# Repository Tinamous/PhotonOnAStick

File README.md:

# PhotonOnAStick
Particle Photon Prototyping board on a USB Stick

## Currently untested (11 July 2015). PCBs ordered for testing.

## Use Case

* Prototype post breadboard. 
* Connection of sensors, LEDs, SparkFun style breakout boards etc.
* Deployed Thing on a Stick where the Photon may be used to make an internet connected sensor for a room, or lighting or ??? and can be plugged into a USB wall adaptor.
* Using readily available wall plugs board may be connected:
** with the board vertical, Photon facing outwards flat to the wall.
** with the board horizontal, Photon facing upwards. 
* These options makes for a nice option for uplighting (internet controlled nightlight?), or a room sensor.
* Other power adaptors exist, e.g. USB in a multi-gang outlet.

## Usage

* USB powered by plugging into a USB A socket on a USB Wall Adaptor, or A -> Micro B on the Particle Photon. Do not connect both at once.
* Top layer is mainly for 0805 devices (and through hole).
* Bottom layer is for 1206 devices (and through hole).

## Botton (looking at the baord with USB connector to the left)
* A0-A7 Analog signals come out to the option of a round test point (solder connection) via an 0805. Can be resistor, 0 ohm link or ....
* A0-A7 Analog signals also come out to a 1206 package with the other side unconnected so this can have a wire tacked on as needed.
** This arrangement may be used to provide either imput impedance/capacitance filter to the analog signal, 
** or by connecting the unterminated end to GND or 3V3 this can provice half of a potential divider for a sensor - the sensor may be providing the other half.
* +5V, Gnd, Tx and Rx come out to a 1206 only. Allows for a resitor and/or wire tacking.

## Center
* Top layer in the middle is a SO16 package outline, can be used for SO8 or anything that would fit. Pins 1-8 go to connectors by the USB port, 9-16 by the bottom of the Photon.
* Top 2 connectors in the middle of the Photon have +5V, +3V3 and Gnd available.

## Top (looking at the baord with USB connector to the left)
* 3v3, VBat and Gnd brought out to 4 pin connector. Pin 2 unconnected (may be used for polarity).
* D0-D7 connected to 1206 package on bottom layer with other end unconnected available for wire.
* D0-D7 on top layer go to 0805 package which is liked to a second 0805 with the far end connected to ground.
** This arrangement allows D0-D7 to be connected to a (0805) LED then a (0805)current limiting resitor on the top layer
** or to provide a pull down where the input is connected to the middle of the pins 0805 packages.

## Prototyping area (Right hand side looking at the baord with USB connector to the left).
* Top rail is 3v3 from the Photon (3)
* Second rail down is GND (G)
* Bottom rail is +5V (5)
* 3V3 and GND have a 0805 connection for a capacitor.
* Each pair of rows have possible connection for 0805 and 1206 device near the Photon to allow for capacitor, resistor or LED.
* Only power rails are connected hole to hole.
* 8 1206 or 8 * 2 0805s are available on the right, again for LEDs, Sensors, Resistors or Capacitors. 
** The 2x 0805 combination allows for a LED + resistor. Either side of the 1206 or 0805 pair are connected to the pins to the outside of them.

## Spark Photon
* This board is designed for the Particle Photon. It does need headers though.
* The Particle Core (Spark Core) may also be used.

## Eagle Libraries Used:

Particle Photon Library: https://github.com/spark/photon/tree/master/libraries
SparkFun: https://github.com/sparkfun/SparkFun-Eagle-Libraries

## Versioning

* Board will have multiple major versions. e.g.
** V1 A0-A8 1206/0805's unterminated.
** V1.x bug fixes for V1 board.

** V2 A0-A8 1206/0805's terminated with +5 or GND based on layer
** V2.x bug fixes for V2 board.

## Ideas

### Different versions

* Change A0-A8 1206 packages so unconnected end is connected to 
* Much narrower (just room for Photon)
* Wonly - USB port at Top Right corner to allow for top exit wall adaptors where USB socket is perpendicular to the wall.
* Surface mount photon

* Timer version. LED/LCD/OLED dispay. Sensor to allow for setting and starting of timer (Hands free)

## Bugs

* Missing Open Hardware Logo.

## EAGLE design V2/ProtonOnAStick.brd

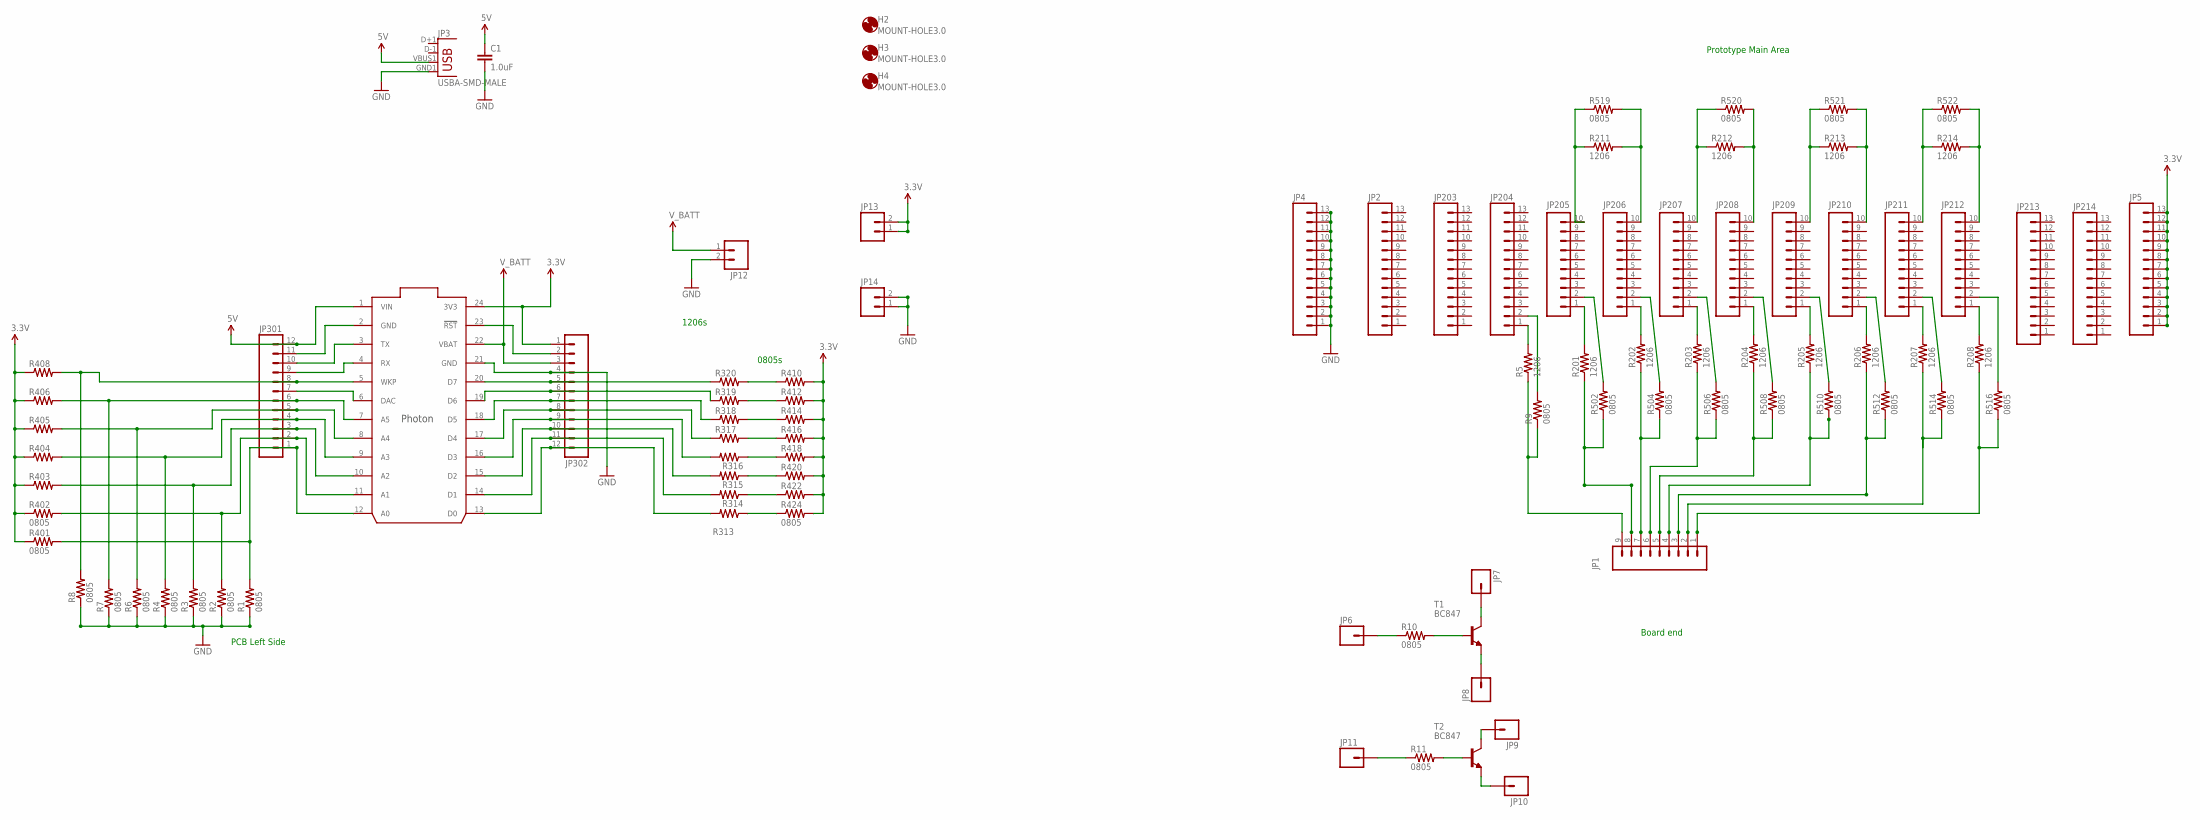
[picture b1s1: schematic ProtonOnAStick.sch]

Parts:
C1: 1.0uF; 0805-CAP
H2, H3, H4: MOUNT-HOLE3.0; 3,0
IC1: PHOTON_WITH_HEADERS; PHOTON
JP1: M09; 1X09
JP2, JP4, JP5, JP203, JP204, JP213, JP214: M13; 1X13
JP3: USBA-SMD-MALE; USB-A-SMT-MALE
JP6, JP7, JP8, JP9, JP10, JP11: M01PTH; 1X01
JP12: M02JST-PTH-2; JST-2-PTH
JP13, JP14: M02PTH; 1X02
JP205, JP206, JP207, JP208, JP209, JP210, JP211, JP212: M10SILK_FEMALE_PTH; 1X10
JP301, JP302: M12PTH; 1X12
R1, R2, R3, R4, R6, R7, R8, R9, R10, R11, R401, R402, R403, R404, R405, R406, R408, R410, R412, R414, R416, R418, R420, R422, R424, R502, R504, R506, R508, R510, R512, R514, R516, R519, R520, R521, R522: 0805
R5, R201, R202, R203, R204, R205, R206, R207, R208, R211, R212, R213, R214, R313, R314, R315, R316, R317, R318, R319, R320: 1206
T1, T2: BC847; SOT23

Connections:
3.3V: IC1.24 (3V3), JP5.1, JP5.2, JP5.3, JP5.4, JP5.5, JP5.6, JP5.7, JP5.8, JP5.9, JP5.10, JP5.11, JP5.12, JP5.13, JP13.1, JP13.2, JP302.1, R401.1, R402.1, R403.1, R404.1, R405.1, R406.1, R408.1, R410.2, R412.2, R414.2, R416.2, R418.2, R420.2, R422.2, R424.2
5V: C1.1, IC1.1 (VIN), JP3.VBUS1 (VBUS), JP301.12
GND: C1.2, IC1.2 (GND), IC1.21 (GND), JP3.GND1 (GND), JP4.1, JP4.2, JP4.3, JP4.4, JP4.5, JP4.6, JP4.7, JP4.8, JP4.9, JP4.10, JP4.11, JP4.12, JP4.13, JP12.2, JP14.1, JP14.2, JP301.11, JP302.4, R1.1, R2.1, R3.1, R4.1, R6.1, R7.1, R8.1
unnamed: JP6.1, R10.1
unnamed: JP206.1, R202.2
unnamed: JP204.1, R5.2
unnamed: IC1.3 (TX), JP301.10
unnamed: IC1.4 (RX), JP301.9
unnamed: IC1.5 (WKP), JP301.8, R8.2, R408.2
unnamed: IC1.6 (DAC), JP301.7
unnamed: IC1.7 (A5), JP301.6, R7.2, R406.2
unnamed: IC1.8 (A4), JP301.5, R6.2, R405.2
unnamed: IC1.9 (A3), JP301.4, R4.2, R404.2
unnamed: IC1.10 (A2), JP301.3, R3.2, R403.2
unnamed: IC1.11 (A1), JP301.2, R2.2, R402.2
unnamed: IC1.12 (A0), JP301.1, R1.2, R401.2
unnamed: JP1.9, R5.1, R9.1
unnamed: R10.2, T1.1 (B)
unnamed: IC1.18 (D5), JP302.7, R318.1
unnamed: IC1.17 (D4), JP302.8, R317.1
unnamed: IC1.16 (D3), JP302.9, R316.2
unnamed: IC1.15 (D2), JP302.10, R315.2
unnamed: IC1.14 (D1), JP302.11, R314.2
unnamed: IC1.13 (D0), JP302.12, R313.2
unnamed: JP209.1, R205.2
unnamed: JP211.2, R514.2
unnamed: IC1.23 (!RST), JP302.2
unnamed: R320.2, R410.1
unnamed: JP207.1, R203.2
unnamed: JP208.1, R204.2
unnamed: JP1.7, R202.1, R504.1
unnamed: JP1.6, R203.1, R506.1
unnamed: JP1.5, R204.1, R508.1
unnamed: JP1.4, R205.1, R510.1
unnamed: JP205.1, R201.2
unnamed: JP1.8, R201.1, R502.1
unnamed: JP210.1, R206.2
unnamed: JP211.1, R207.2
unnamed: JP1.3, R206.1, R512.1
unnamed: JP1.2, R207.1, R514.1
unnamed: IC1.20 (D7), JP302.5, R320.1
unnamed: IC1.19 (D6), JP302.6, R319.1
unnamed: JP212.2, R516.2
unnamed: JP7.1, T1.3 (C)
unnamed: JP210.2, R512.2
unnamed: R313.1, R424.1
unnamed: R314.1, R422.1
unnamed: R315.1, R420.1
unnamed: R316.1, R418.1
unnamed: R317.2, R416.1
unnamed: R318.2, R414.1
unnamed: R319.2, R412.1
unnamed: JP209.2, R510.2
unnamed: JP206.2, R504.2
unnamed: JP205.2, R502.2
unnamed: JP207.2, R506.2
unnamed: JP8.1, T1.2 (E)
unnamed: JP212.1, R208.2
unnamed: JP1.1, R208.1, R516.1
unnamed: JP204.2, R9.2
unnamed: JP11.1, R11.1
unnamed: R11.2, T2.1 (B)
unnamed: JP9.1, T2.3 (C)
unnamed: JP10.1, T2.2 (E)
unnamed: JP205.10, R211.1, R519.1
unnamed: JP206.10, R211.2, R519.2
unnamed: JP208.10, R212.2, R520.2
unnamed: JP210.10, R213.2, R521.2
unnamed: JP212.10, R214.2, R522.2
unnamed: JP207.10, R212.1, R520.1
unnamed: JP209.10, R213.1, R521.1
unnamed: JP211.10, R214.1, R522.1
unnamed: JP208.2, R508.2
V_BATT: IC1.22 (VBAT), JP12.1, JP302.3

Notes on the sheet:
PCB Left Side
Prototype Main Area
0805s
1206s
Board end

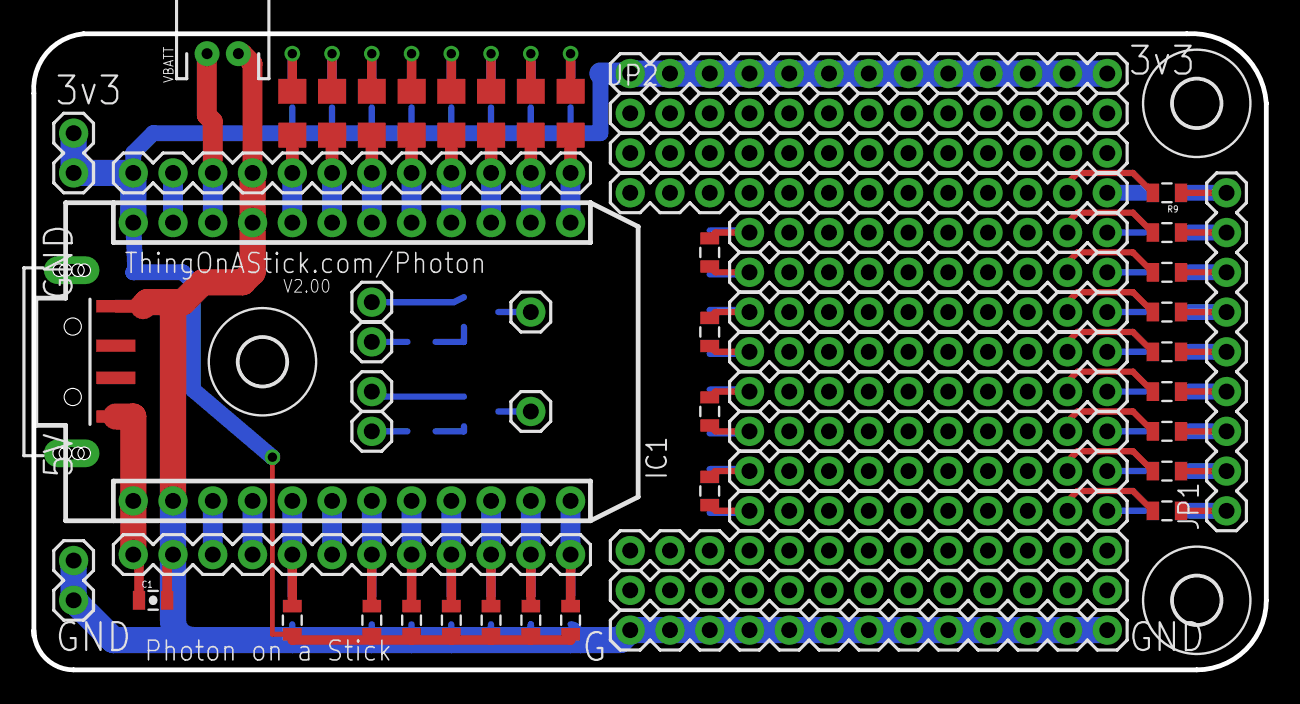
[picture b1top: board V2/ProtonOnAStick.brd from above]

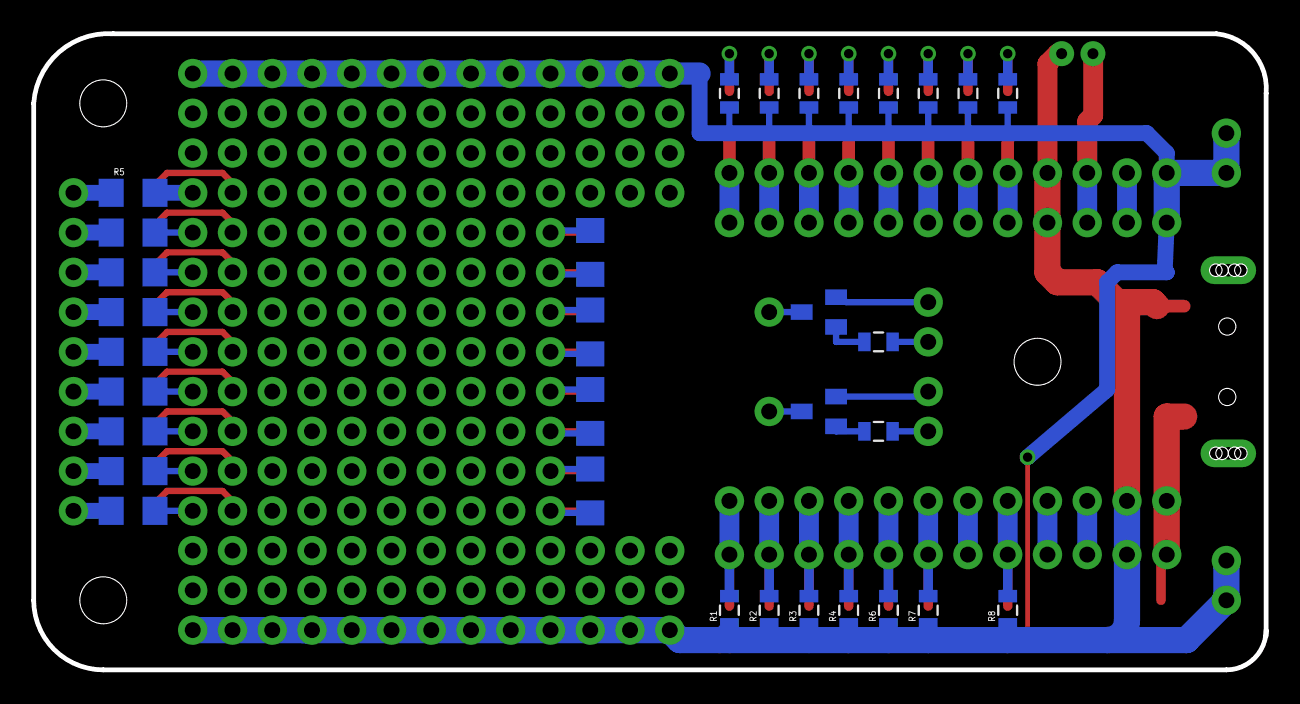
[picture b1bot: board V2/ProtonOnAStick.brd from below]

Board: 2 copper layers, 78.8 x 40.6 mm, 93 parts (32 on the bottom side), 74 nets.

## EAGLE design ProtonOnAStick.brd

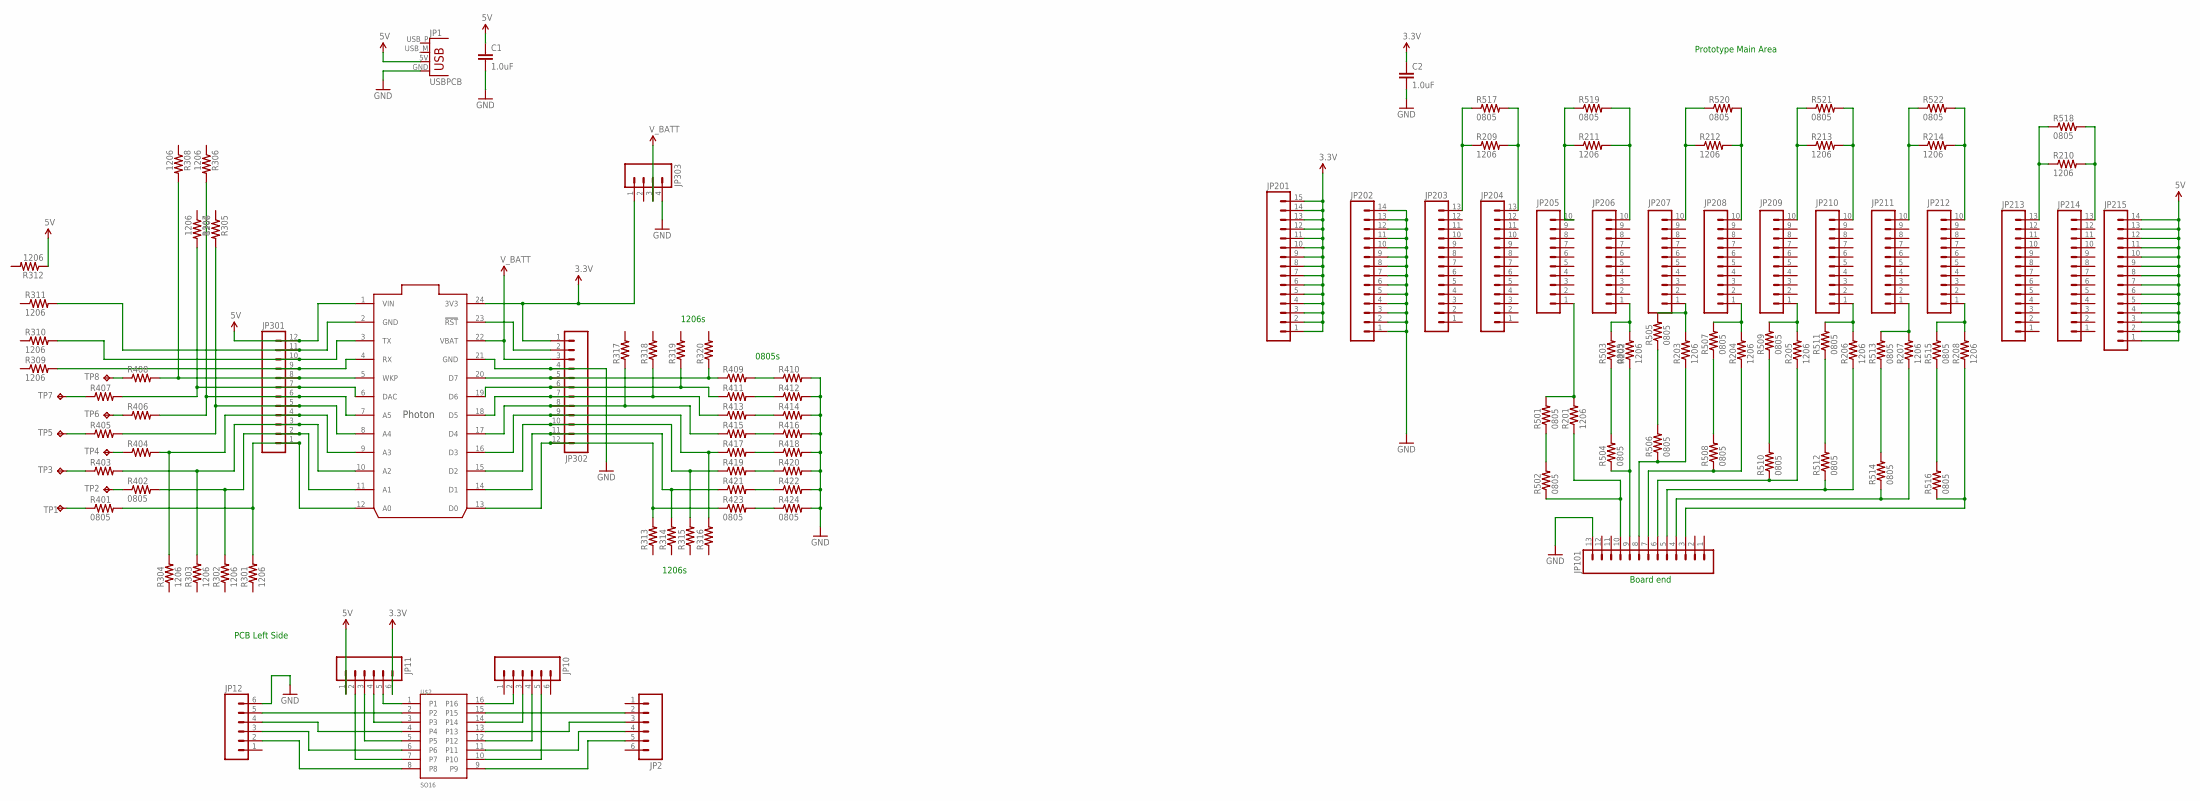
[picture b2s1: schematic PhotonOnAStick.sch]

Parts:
C1, C2: 1.0uF; 0805-CAP
JP1: USBPCB; USB-A-PCB
JP2, JP10, JP11, JP12: M06SILK_FEMALE_PTH; 1X06
JP101, JP203, JP204, JP213, JP214: M13; 1X13
JP201: M15; 1X15
JP202, JP215: M14; 1X14
JP205, JP206, JP207, JP208, JP209, JP210, JP211, JP212: M10SILK_FEMALE_PTH; 1X10
JP301, JP302: M12PTH; 1X12
JP303: M04PTH; 1X04
R201, R202, R203, R204, R205, R206, R207, R208, R209, R210, R211, R212, R213, R214, R301, R302, R303, R304, R305, R306, R307, R308, R309, R310, R311, R312, R313, R314, R315, R316, R317, R318, R319, R320: 1206
R401, R402, R403, R404, R405, R406, R407, R408, R409, R410, R411, R412, R413, R414, R415, R416, R417, R418, R419, R420, R421, R422, R423, R424, R501, R502, R503, R504, R505, R506, R507, R508, R509, R510, R511, R512, R513, R514, R515, R516, R517, R518, R519, R520, R521, R522: 0805
TP1, TP2, TP3, TP4, TP5, TP6, TP7, TP8: TPB1,27; B1,27
U$1: PHOTON_WITH_HEADERS; PHOTON
U$2: SO16

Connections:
3.3V: C2.1, JP11.6, JP201.1, JP201.2, JP201.3, JP201.4, JP201.5, JP201.6, JP201.7, JP201.8, JP201.9, JP201.10, JP201.11, JP201.12, JP201.13, JP201.14, JP201.15, JP302.1, JP303.1, U$1.24 (3V3)
5V: C1.1, JP1.5V (VBUS), JP11.1, JP215.1, JP215.2, JP215.3, JP215.4, JP215.5, JP215.6, JP215.7, JP215.8, JP215.9, JP215.10, JP215.11, JP215.12, JP215.13, JP215.14, JP301.12, R312.1, U$1.1 (VIN)
GND: C1.2, C2.2, JP1.GND, JP12.6, JP101.13, JP202.1, JP202.2, JP202.3, JP202.4, JP202.5, JP202.6, JP202.7, JP202.8, JP202.9, JP202.10, JP202.11, JP202.12, JP202.13, JP202.14, JP302.4, JP303.4, R410.2, R412.2, R414.2, R416.2, R418.2, R420.2, R422.2, R424.2, U$1.21 (GND)
unnamed: JP214.13, R210.2, R518.2
unnamed: JP206.1, R202.2, R503.2
unnamed: JP301.11, R311.2, U$1.2 (GND)
unnamed: JP301.10, R310.2, U$1.3 (TX)
unnamed: JP301.9, R309.2, U$1.4 (RX)
unnamed: JP301.8, R308.2, R408.2, U$1.5 (WKP)
unnamed: JP301.7, R307.2, R407.2, U$1.6 (DAC)
unnamed: JP301.6, R306.2, R406.2, U$1.7 (A5)
unnamed: JP301.5, R305.2, R405.2, U$1.8 (A4)
unnamed: JP301.4, R304.2, R404.2, U$1.9 (A3)
unnamed: JP301.3, R303.2, R403.2, U$1.10 (A2)
unnamed: JP301.2, R302.2, R402.2, U$1.11 (A1)
unnamed: JP301.1, R301.2, R401.2, U$1.12 (A0)
unnamed: JP204.13, R209.2, R517.2
unnamed: JP213.13, R210.1, R518.1
unnamed: JP302.7, R318.1, R413.1, U$1.18 (D5)
unnamed: JP302.8, R317.1, R415.1, U$1.17 (D4)
unnamed: JP302.9, R316.2, R417.1, U$1.16 (D3)
unnamed: JP302.10, R315.2, R419.1, U$1.15 (D2)
unnamed: JP302.11, R314.2, R421.1, U$1.14 (D1)
unnamed: JP302.12, R313.2, R423.1, U$1.13 (D0)
unnamed: JP209.1, R205.2, R509.2
unnamed: R513.1, R514.2
unnamed: JP302.2, U$1.23 (!RST)
unnamed: R409.2, R410.1
unnamed: JP207.1, R203.2, R505.2
unnamed: JP208.1, R204.2, R507.2
unnamed: JP101.9, R202.1, R504.1
unnamed: JP101.8, R203.1, R506.1
unnamed: JP101.7, R204.1, R508.1
unnamed: JP101.6, R205.1, R510.1
unnamed: JP205.1, R201.2, R501.2
unnamed: JP101.10, R201.1, R502.1
unnamed: JP210.1, R206.2, R511.2
unnamed: JP211.1, R207.2, R513.2
unnamed: JP101.5, R206.1, R512.1
unnamed: JP101.4, R207.1, R514.1
unnamed: JP302.5, R320.1, R409.1, U$1.20 (D7)
unnamed: JP302.6, R319.1, R411.1, U$1.19 (D6)
unnamed: R515.1, R516.2
unnamed: R511.1, R512.2
unnamed: R423.2, R424.1
unnamed: R421.2, R422.1
unnamed: R419.2, R420.1
unnamed: R417.2, R418.1
unnamed: R415.2, R416.1
unnamed: R413.2, R414.1
unnamed: R411.2, R412.1
unnamed: R509.1, R510.2
unnamed: R503.1, R504.2
unnamed: R501.1, R502.2
unnamed: R505.1, R506.2
unnamed: JP203.13, R209.1, R517.1
unnamed: JP212.1, R208.2, R515.2
unnamed: JP101.3, R208.1, R516.1
unnamed: R408.1, TP8.TP
unnamed: R407.1, TP7.TP
unnamed: R405.1, TP5.TP
unnamed: R404.1, TP4.TP
unnamed: R403.1, TP3.TP
unnamed: R401.1, TP1.TP
unnamed: R402.1, TP2.TP
unnamed: R406.1, TP6.TP
unnamed: JP205.10, R211.1, R519.1
unnamed: JP206.10, R211.2, R519.2
unnamed: JP208.10, R212.2, R520.2
unnamed: JP210.10, R213.2, R521.2
unnamed: JP212.10, R214.2, R522.2
unnamed: JP207.10, R212.1, R520.1
unnamed: JP209.10, R213.1, R521.1
unnamed: JP211.10, R214.1, R522.1
unnamed: JP11.5, U$2.1
unnamed: JP11.4, U$2.3
unnamed: JP11.3, U$2.5
unnamed: JP11.2, U$2.7
unnamed: JP12.5, U$2.2
unnamed: JP12.4, U$2.4
unnamed: JP12.3, U$2.6
unnamed: JP12.2, U$2.8
unnamed: JP10.2, U$2.16
unnamed: JP2.2, U$2.15
unnamed: JP10.3, U$2.14
unnamed: JP10.4, U$2.12
unnamed: JP10.5, U$2.10
unnamed: JP2.3, U$2.13
unnamed: JP2.4, U$2.11
unnamed: JP2.5, U$2.9
unnamed: R507.1, R508.2
V_BATT: JP302.3, JP303.3, U$1.22 (VBAT)

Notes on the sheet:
PCB Left Side
Prototype Main Area
0805s
1206s
Board end

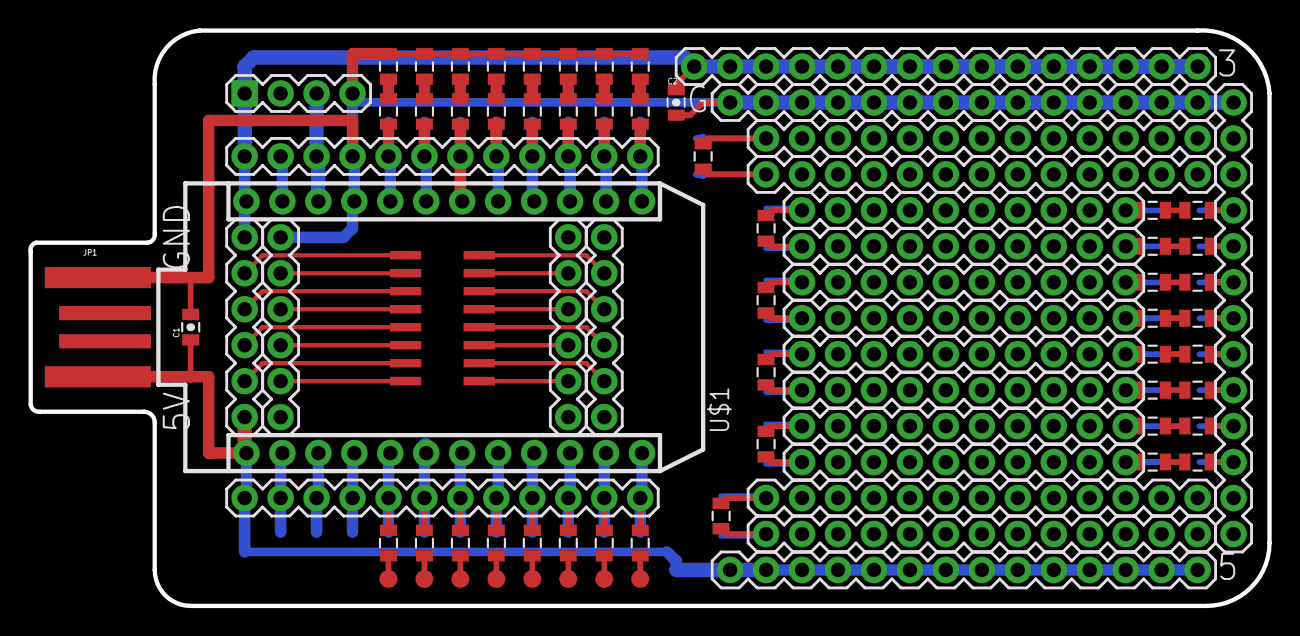
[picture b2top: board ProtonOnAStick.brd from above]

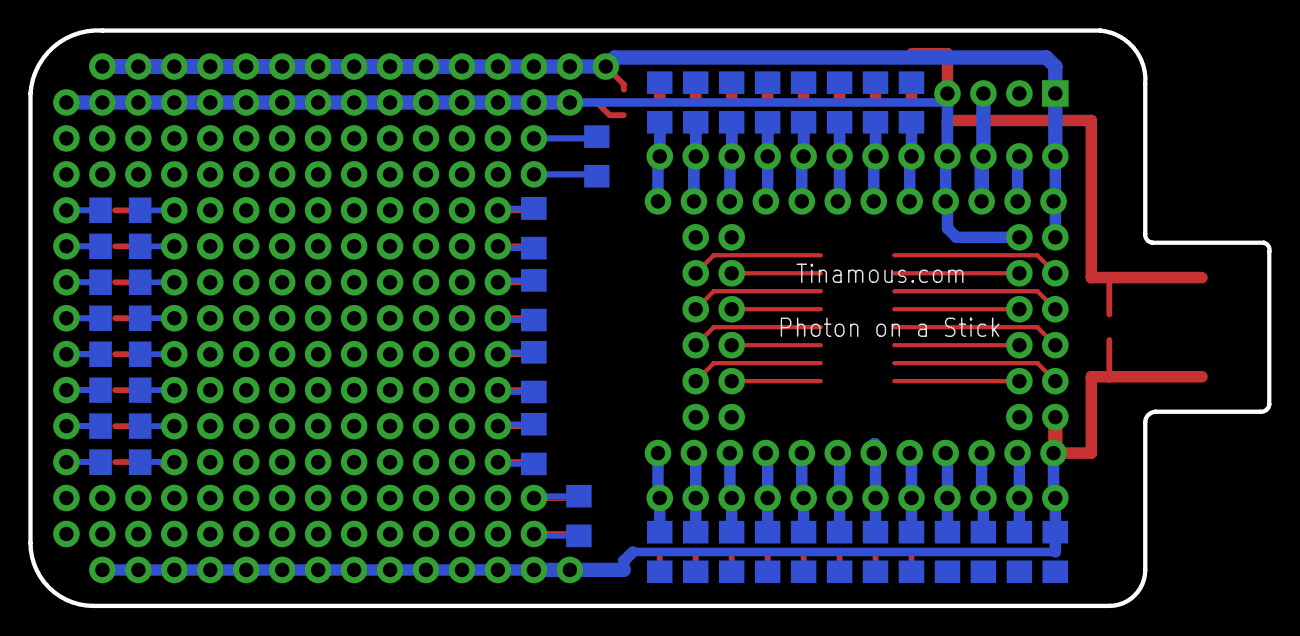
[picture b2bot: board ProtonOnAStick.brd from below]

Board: 2 copper layers, 87.5 x 40.6 mm, 116 parts (34 on the bottom side), 92 nets.

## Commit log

2015-07-11 Initial version.
2015-07-11 Fixed filename naming
2015-07-11 Added readme
2015-07-11 Added pdf's of schematic and PCB top/bottom
2015-09-08 Added V2 boards.

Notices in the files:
parts and their libraries:
SparkFun-Connectors: Licensing: Creative Commons ShareAlike 4.0 International - https://creativecommons.org/licenses/by-sa/4.0
